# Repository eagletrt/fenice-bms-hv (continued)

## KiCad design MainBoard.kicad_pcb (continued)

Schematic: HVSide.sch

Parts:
C16, C23, C24, C26, C27, C40, C41, C44: 100nF; C_0603_1608Metric
C17: 1uF; C_0805_2012Metric
C42: 6.8uF; C_0805_2012Metric
C43: 10nF; C_0603_1608Metric
C45, C46: 10uF; C_0805_2012Metric
D4: LED_Small; LED_0603_1608Metric_Castellated
J4, J11: CONN_2X2; Molex_Micro-Fit_3.0_43045-0412_2x02_P3.00mm_Vertical
J17: HV; Molex_Mega-Fit_76829-0104_2x02_P5.70mm_Vertical
J18, J19: CONN_1X2; Molex_Micro-Fit_3.0_43650-0215_1x02_P3.00mm_Vertical
R10, R18, R26, R29, R57, R71: 100K; R_0603_1608Metric
R21, R59: 1K; R_0603_1608Metric
R24, R27: 10K; R_0603_1608Metric
R31, R32: 22; R_0603_1608Metric
R56, R64, R66: 10M; R_1206_3216Metric
R65, R67: 71K5; R_0603_1608Metric
R69: 2K; R_0603_1608Metric
R70: 680; R_0603_1608Metric
U7: ADCMP354; Analog_KS-4
U10: DCDC_ISO_5V_ISO; DC_DC_ISO_ROExxxx
U15: CD4082; TSSOP-14_4.4x5mm_P0.65mm
U16: ADCMP350; Analog_KS-4
U19, U26: TCMT1103; SOP-4_4.4x2.6mm_P1.27mm
U23: CD4072BPW; TSSOP-14_4.4x5mm_P0.65mm
U24: LTC6259; TSOT-23-8
U27: DCDC_ISO_5V; RFMM
U28: MIC5365-3.3YC5; SOT-353_SC-70-5
U29: Si8900; SOIC-16W_7.5x10.3mm_P1.27mm
U30: MAX14878AWA+; SOIC-8_7.5x5.85mm_P1.27mm

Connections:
+3V3: C16.1, C40.1, U29.10 (VDDB), U29.16 (VDDB), U30.3 (VDD1); also elsewhere on the board
+5V: C42.1, U27.1 (VIN+); also elsewhere on the board
+12V: C41.1, R24.1, R26.1, U15.4, U15.5, U15.14 (VCC), U23.14 (VDD); also elsewhere on the board
+BATT: J17.4, R64.2; also elsewhere on the board
+TS: J17.3, J18.1, J18.2, R56.1, R66.2; also elsewhere on the board
-BATT: C17.2, C23.2, C24.2, C26.2, C27.2, C44.2, C45.2, C46.2, J11.3, J17.1, R65.2, R67.2, U7.2 (GND), U10.3 (VOUT-), U16.2 (GND), U24.4, U26.3, U27.5 (VOUT-), U28.2 (GND), U29.8 (GNDA), U30.5 (GND2)
-TS: J17.2, J19.1, J19.2, R57.2
/AMS/ADC_RX: R32.1; also elsewhere on the board
/AMS/ADC_SIN: R29.1, R70.1; also elsewhere on the board
/AMS/ADC_TX: R31.1; also elsewhere on the board
/AMS/ISO_CAN_RX: U30.1 (RXD); also elsewhere on the board
/AMS/ISO_CAN_TX: U30.2 (TXD); also elsewhere on the board
/FB_AIR+: U23.3, U23.11; also elsewhere on the board
/FB_AIR-: U23.4, U23.10; also elsewhere on the board
/FB_TS_OVER_60V: R24.2, U15.2, U19.4, U23.5, U23.9; also elsewhere on the board
/HV/3V3ISO: C43.1, C46.1, R69.1, U28.5 (VOUT), U29.1 (VDDA)
/HV/5VISO: C26.1, C27.1, C44.1, C45.1, J11.4, R21.2, R71.2, U7.4 (VCC), U24.8, U27.7 (VOUT+), U28.1 (VIN), U30.8 (VCC2)
/HV/5V_FROM_CELL: C17.1, R59.1, U10.4 (VOUT+), U16.4 (VCC)
/HV/EXT_5V: J4.3, U10.2 (VIN+)
/HV/EXT_GND: J4.1, U10.1 (VIN-)
/HV/PRECHARGE_ON: U15.3; also elsewhere on the board
/HV/PRECHARGE_STATUS: R26.2, U15.1, U23.2, U23.12
/HV/PROMINENT+: J4.4, R59.2
/HV/PROMINENT-: J4.2, U16.3
/HV/PackV: R18.2, U24.1, U24.2
/HV/PackV_FT: C24.1, R18.1, U29.4 (AIN1)
/HV/TSV: R10.2, U24.6, U24.7
/HV/TSV_FT: C23.1, R10.1, U29.3 (AIN0)
/HV/TS_DIVIDER: R56.2, R57.1, U7.1 (VIN), U16.1 (VIN)
/HV/~RST~_8902: C43.2, R69.2, U26.4, U29.7 (~RST)
/IM: J11.1, U30.6 (CANL); also elsewhere on the board
/IP: J11.2, U30.7 (CANH); also elsewhere on the board
/LED_INDICATOR: U23.13; also elsewhere on the board
GND: C16.2, C40.2, C41.2, C42.2, R27.1, R29.2, U15.7 (VSS), U19.3, U23.7 (VSS), U26.2, U27.2 (VIN-), U29.9 (GNDB), U30.4 (GND1); also elsewhere on the board
unnamed: D4.1 (K), R27.2
unnamed: D4.2 (A), U23.1
unnamed: R21.1, U19.1
unnamed: R31.2, U29.13 (RX)
unnamed: R32.2, U29.12 (TX)
unnamed: R64.1, R65.1, U24.3
unnamed: R66.1, R67.1, U24.5
unnamed: R70.2, U26.1
unnamed: R71.1, U28.3 (EN)
unnamed: U7.3, U19.2

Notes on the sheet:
UART ISOLATED PACK VOLTAGE ADC
ISOLATED VOLTAGE SOURCES
"IN" connected to the NEGATIVE comparator input INTERNAL Vref=0.6V 1% High voltage (up to 22 V) tolerance on VIN
Prominent Indicator
HV ADC BUFFERS
PRECHARGE_STATUS = TS_exceed_60Vdc && PRECHARGE_ON
"IN" connected to thePOSITIVE comparator input INTERNAL Vref=0.6V 1% High voltage (up to 22 V) tolerance on VIN
IMD_TS-
IMD_TS+
EXT_POWER&PROMIMENT
CAN_ISO
PROMINENT INDICTOR

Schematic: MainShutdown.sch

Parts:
C32, C34, C35, C47: 100nF; C_0603_1608Metric
C33: 1uF; C_0805_2012Metric
D14: 12V; D_SOD-323
D15: D; SOD_323HE
J6, J10: CONN_2X2; Molex_Micro-Fit_3.0_43045-0412_2x02_P3.00mm_Vertical
K1: KT12-1A; KT_THT
K2: G6DN 12V; G6DN-1A_DC12
Q1: SSM3K361TU,LF; SOT-323_SC-70
Q2: TSM2312; TSOT-23
R9: 100K; R_0603_1608Metric
R54: 1M; R_0603_1608Metric
R55: 10K; pwr163
RN13: 100K; R_network_4x1_bourns_CAY16
U4: EL5421T; MSOP-10_3x3mm_P0.5mm
U13: TS3704IPT; TSSOP-14_4.4x5mm_P0.65mm
U14: CD4044; TSSOP-16_4.4x5mm_P0.65mm
U15: CD4082; TSSOP-14_4.4x5mm_P0.65mm

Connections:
+3V3: RN13.2 (R2.1), U13.4 (-); also elsewhere on the board
+12V: C32.1, C34.1, C35.1, C47.1, D15.1 (K), J6.1, J10.4, K2.2, R9.2, RN13.1 (R1.1), U4.3, U13.3 (V+), U14.5 (EN), U14.16 (Vdd), U15.14 (VCC); also elsewhere on the board
+BATT: K1.4; also elsewhere on the board
+TS: R55.2; also elsewhere on the board
/BMS_Fault: U13.7 (+); also elsewhere on the board
/BMS_LED: U4.9; also elsewhere on the board
/BSPD_SIG: U15.9; also elsewhere on the board
/FB_AIR+: J10.3; also elsewhere on the board
/FB_AIR-: J6.2; also elsewhere on the board
/FB_BMS: U13.1, U14.6; also elsewhere on the board
/FB_BMS_SD: U4.2, U15.12; also elsewhere on the board
/FB_IMD_SD: U4.4, U15.11; also elsewhere on the board
/FB_LACTH_BMS: U4.1, U4.10, U14.9; also elsewhere on the board
/FB_LACTH_IMD: U4.5, U4.6, U14.10; also elsewhere on the board
/FB_PC_END: Q1.1 (G), U13.13; also elsewhere on the board
/FB_SD_MINIRELAY: Q2.1 (G), U15.13; also elsewhere on the board
/FB_TS_ON: U13.14, U15.10; also elsewhere on the board
/FROM_SD: K2.3; also elsewhere on the board
/FROM_TSMS: J6.4, J10.1, K1.1, R54.2; also elsewhere on the board
/HV/PRECHARGE_ON: RN13.8 (R1.2), U13.2; also elsewhere on the board
/IMD_Fault: U14.12; also elsewhere on the board
/IMD_LED: U4.7; also elsewhere on the board
/NRST_SD: C33.1, R9.1, U14.7, U14.11; also elsewhere on the board
/PC_ENDED: U13.11 (+); also elsewhere on the board
/Shutdown/LAST_AIR: J10.2, Q1.3 (D)
/Shutdown/VREF_1.5V: RN13.6 (R3.2), RN13.7 (R2.2), U13.6 (-), U13.8 (-), U13.10 (-)
/Shutdown/dissipation: R55.3 (back)
/TO_TSMS: K2.4; also elsewhere on the board
/TS_ON: U13.9 (+); also elsewhere on the board
GND: C32.2, C33.2, C34.2, C35.2, C47.2, D14.2 (A), J6.3, K1.2, Q1.2 (S), Q2.2 (S), RN13.3 (R3.1), U4.8, U13.12 (V-), U14.8 (Vss), U15.7 (VSS); also elsewhere on the board
unnamed: D14.1 (K), R54.1, U13.5 (+)
unnamed: D15.2 (A), K2.1, Q2.3 (D)
unnamed: K1.3, R55.1

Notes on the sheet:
PWR163S-25-1002J
PRE-CHARGE CIRCUIT
TRACTIVE SYSTEM CONTROL
AIR CONTROL CIRCUIT
RESET BUTTON WITH PULLUP (100K) FOR AMS AND IMD FAULT WITH START DELAY OF 120ms (BECAUSE OF C=1uF AND VIH MIN OF 4044 is 8.4V AT VCC=12V)
LACTHING IC
SHUTDOWN STATUS
Vin=12V R=10K-->14.4mW Vref_1V5 R=100K-->0.06mW
AIR+
AIR-
Saves the fault status until reset from: BMS and IMD
TODO: no idea
TODO: still no idea probably for buffering before sending it out through the connector

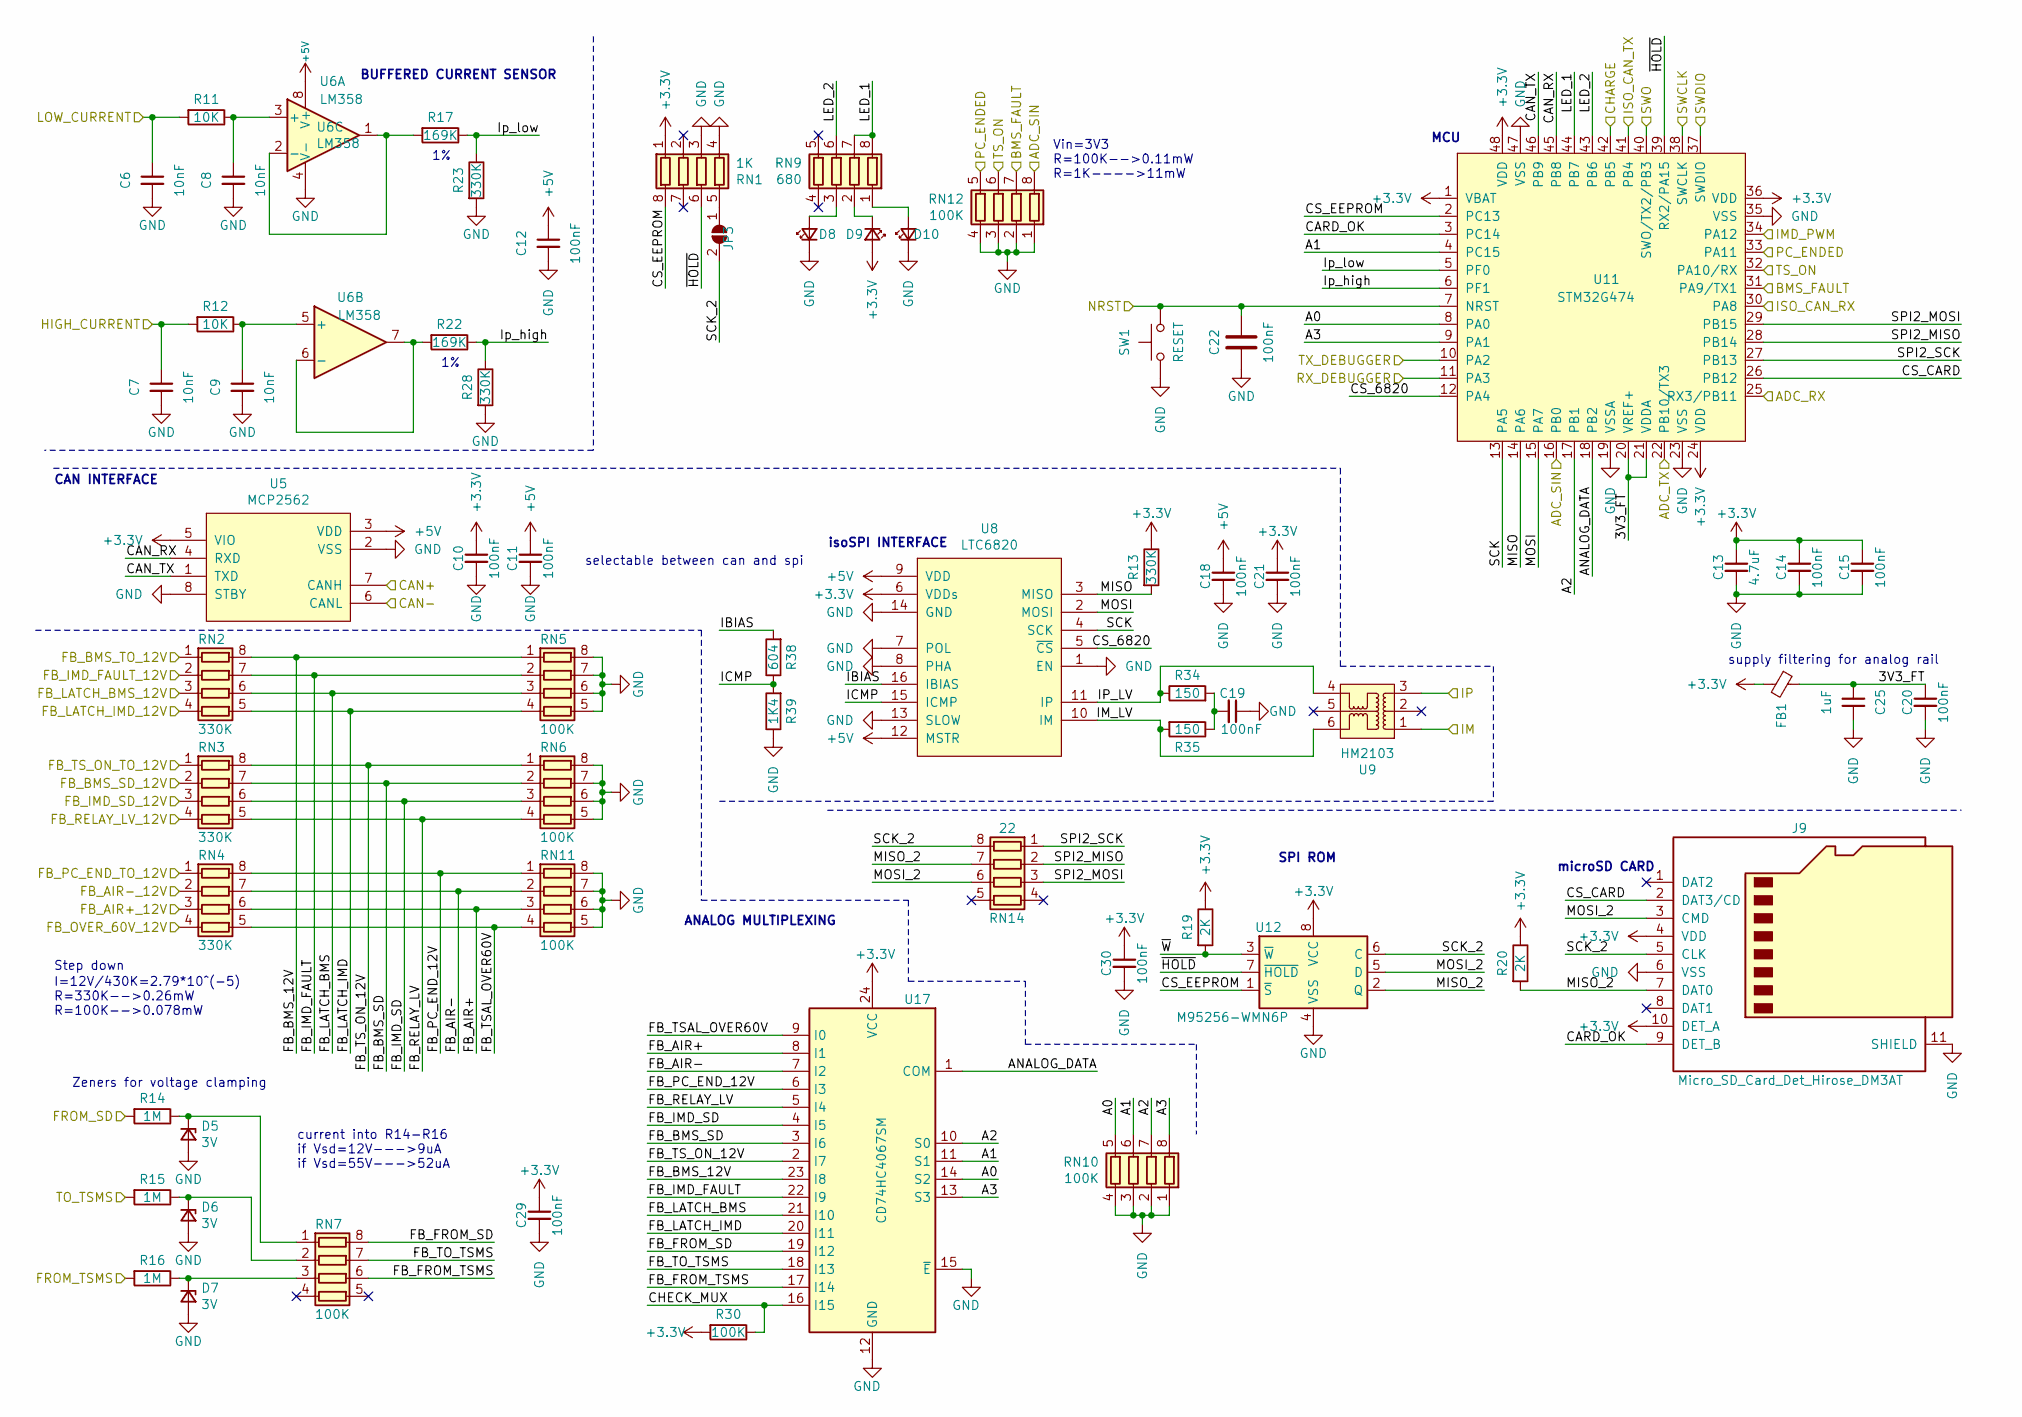
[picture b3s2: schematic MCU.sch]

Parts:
C6, C7, C8, C9: 10nF; C_0603_1608Metric
C10, C11, C12, C14, C15, C18, C19, C20, C21, C22, C29, C30: 100nF; C_0603_1608Metric
C13: 4.7uF; C_0805_2012Metric
C25: 1uF; C_0603_1608Metric
D5, D6, D7: 3V; D_SOD-323
D8: LED_Small; LED_REVERSE_MOUNT_cilindrical
D9, D10: LED_Small; LED_0603_1608Metric_Castellated
FB1: FerriteBead_Small; L_0603_1608Metric_Pad1.05x0.95mm_HandSolder
J9: Micro_SD_Card_Det_Hirose_DM3AT; MicroSD_Hirose_DM3AT-SF-PEJM5
JP3: SolderJumper_2_Open; Jumper_SMD_0603
R11, R12: 10K; R_0603_1608Metric
R13, R23, R28: 330K; R_0603_1608Metric
R14, R15, R16: 1M; R_0603_1608Metric
R17, R22: 169K; R_0603_1608Metric
R19, R20: 2K; R_0603_1608Metric
R30: 100K; R_0603_1608Metric
R34, R35: 150; R_0603_1608Metric
R38: 604; R_0603_1608Metric
R39: 1K4; R_0603_1608Metric
RN1: 1K; R_network_4x1_bourns_CAY16
RN2, RN3, RN4: 330K; R_network_4x1_bourns_CAY16
RN5, RN6, RN7, RN10, RN11, RN12: 100K; R_network_4x1_bourns_CAY16
RN9: 680; R_network_4x1_bourns_CAY16
RN14: 22; R_network_4x1_bourns_CAY16
SW1: RESET; Button_SMD_6x3.5x4.3mm
U5: MCP2562; SOIC-8_3.9x4.9mm_P1.27mm
U6: LM358; TSOT-23-8
U8: LTC6820; MSOP-16
U9: HM2103
U11: STM32G474; LQFP-48_7x7mm_P0.5mm
U12: M95256-WMN6P; TSSOP-8_4.4x3mm_P0.65mm
U17: CD74HC4067SM; TSSOP-24_4.4x7.8mm_P0.65mm

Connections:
+3V3: C10.1, C13.1, C14.1, C15.1, C21.1, C29.1, C30.1, D9.2 (A), FB1.2, J9.4 (VDD), J9.10 (DET_A), R13.1, R19.1, R20.1, R30.2, RN1.1 (R1.1), U5.5 (VIO), U8.6 (VDDs), U11.1 (VBAT), U11.24 (VDD), U11.36 (VDD), U11.48 (VDD), U12.8 (VCC), U17.24 (VCC); also elsewhere on the board
+5V: C11.1, C12.1, C18.1, U5.3 (VDD), U6.8 (V+), U8.9 (VDD), U8.12 (MSTR); also elsewhere on the board
/AMS/3V3_FT: C20.1, C25.2, FB1.1, U11.20 (VREF+), U11.21 (VDDA)
/AMS/A0: RN10.5 (R4.2), U11.8 (PA0), U17.14 (S2)
/AMS/A1: RN10.6 (R3.2), U11.4 (PC15), U17.11 (S1)
/AMS/A2: RN10.7 (R2.2), U11.17 (PB1), U17.10 (S0)
/AMS/A3: RN10.8 (R1.2), U11.9 (PA1), U17.13 (S3)
/AMS/ADC_RX: U11.25 (RX3/PB11); also elsewhere on the board
/AMS/ADC_SIN: RN12.8 (R1.2), U11.16 (PB0); also elsewhere on the board
/AMS/ADC_TX: U11.22 (PB10/TX3); also elsewhere on the board
/AMS/ANALOG_DATA: U11.18 (PB2), U17.1 (COM)
/AMS/CAN_RX: U5.4 (RXD), U11.45 (PB8)
/AMS/CAN_TX: U5.1 (TXD), U11.46 (PB9)
/AMS/CARD_OK: J9.9 (DET_B), U11.3 (PC14)
/AMS/CHECK_MUX: R30.1, U17.16 (I15)
/AMS/CS_6820: U8.5 (~CS), U11.12 (PA4)
/AMS/CS_CARD: J9.2 (DAT3/CD), U11.26 (PB12)
/AMS/CS_EEPROM: RN1.8 (R1.2), U11.2 (PC13), U12.1 (~S)
/AMS/FB_AIR+: RN4.6 (R3.2), RN11.3 (R3.1), U17.8 (I1)
/AMS/FB_AIR-: RN4.7 (R2.2), RN11.2 (R2.1), U17.7 (I2)
/AMS/FB_BMS_12V: RN2.8 (R1.2), RN5.1 (R1.1), U17.23 (I8)
/AMS/FB_BMS_SD: RN3.7 (R2.2), RN6.2 (R2.1), U17.3 (I6)
/AMS/FB_FROM_SD: RN7.8 (R1.2), U17.19 (I12)
/AMS/FB_FROM_TSMS: RN7.6 (R3.2), U17.17 (I14)
/AMS/FB_IMD_FAULT: RN2.7 (R2.2), RN5.2 (R2.1), U17.22 (I9)
/AMS/FB_IMD_SD: RN3.6 (R3.2), RN6.3 (R3.1), U17.4 (I5)
/AMS/FB_LATCH_BMS: RN2.6 (R3.2), RN5.3 (R3.1), U17.21 (I10)
/AMS/FB_LATCH_IMD: RN2.5 (R4.2), RN5.4 (R4.1), U17.20 (I11)
/AMS/FB_PC_END_12V: RN4.8 (R1.2), RN11.1 (R1.1), U17.6 (I3)
/AMS/FB_RELAY_LV: RN3.5 (R4.2), RN6.4 (R4.1), U17.5 (I4)
/AMS/FB_TO_TSMS: RN7.7 (R2.2), U17.18 (I13)
/AMS/FB_TSAL_OVER60V: RN4.5 (R4.2), RN11.4 (R4.1), U17.9 (I0)
/AMS/FB_TS_ON_12V: RN3.8 (R1.2), RN6.1 (R1.1), U17.2 (I7)
/AMS/IBIAS: R38.2, U8.16 (IBIAS)
/AMS/ICMP: R38.1, R39.2, U8.15 (ICMP)
/AMS/IM_LV: R35.2, U8.10 (IM), U9.6
/AMS/IP_LV: R34.1, U8.11 (IP), U9.4
/AMS/ISO_CAN_RX: U11.30 (PA8); also elsewhere on the board
/AMS/ISO_CAN_TX: U11.41 (PB4); also elsewhere on the board
/AMS/Ip_high: R22.1, R28.1, U11.6 (PF1)
/AMS/Ip_low: R17.1, R23.1, U11.5 (PF0)
/AMS/LED_1: RN9.7 (R2.2), RN9.8 (R1.2), U11.44 (PB7)
/AMS/LED_2: RN9.6 (R3.2), U11.43 (PB6)
/AMS/MISO: R13.2, U8.3 (MISO), U11.14 (PA6)
/AMS/MISO_2: J9.7 (DAT0), R20.2, RN14.7 (R2.2), U12.2 (Q)
/AMS/MOSI: U8.2 (MOSI), U11.15 (PA7)
/AMS/MOSI_2: J9.3 (CMD), RN14.6 (R3.2), U12.5 (D)
/AMS/SCK: U8.4 (SCK), U11.13 (PA5)
/AMS/SCK_2: J9.5 (CLK), JP3.2 (B), RN14.8 (R1.2), U12.6 (C)
/AMS/SPI2_MISO: RN14.2 (R2.1), U11.28 (PB14)
/AMS/SPI2_MOSI: RN14.3 (R3.1), U11.29 (PB15)
/AMS/SPI2_SCK: RN14.1 (R1.1), U11.27 (PB13)
/AMS/~HOLD~: RN1.6 (R3.2), U11.39 (RX2/PA15), U12.7 (~HOLD)
/AMS/~W~: R19.2, U12.3 (~W)
/BMS_Fault: RN12.7 (R2.2), U11.31 (PA9/TX1); also elsewhere on the board
/CAN+: U5.7 (CANH); also elsewhere on the board
/CAN-: U5.6 (CANL); also elsewhere on the board
/CHARGE: U11.42 (PB5); also elsewhere on the board
/FB_AIR+: RN4.3 (R3.1); also elsewhere on the board
/FB_AIR-: RN4.2 (R2.1); also elsewhere on the board
/FB_BMS: RN2.1 (R1.1); also elsewhere on the board
/FB_BMS_SD: RN3.2 (R2.1); also elsewhere on the board
/FB_IMD_SD: RN3.3 (R3.1); also elsewhere on the board
/FB_LACTH_BMS: RN2.3 (R3.1); also elsewhere on the board
/FB_LACTH_IMD: RN2.4 (R4.1); also elsewhere on the board
/FB_PC_END: RN4.1 (R1.1); also elsewhere on the board
/FB_SD_MINIRELAY: RN3.4 (R4.1); also elsewhere on the board
/FB_TS_ON: RN3.1 (R1.1); also elsewhere on the board
/FB_TS_OVER_60V: RN4.4 (R4.1); also elsewhere on the board
/FROM_SD: R14.2; also elsewhere on the board
/FROM_TSMS: R16.2; also elsewhere on the board
/HIGH_CURRENT: C7.1, R12.2; also elsewhere on the board
/IM: U9.1; also elsewhere on the board
/IMD: U11.34 (PA12); also elsewhere on the board
/IMD_Fault: RN2.2 (R2.1); also elsewhere on the board
/IP: U9.3; also elsewhere on the board
/LOW_CURRENT: C6.1, R11.2; also elsewhere on the board
/NRST_MCU: C22.1, SW1.1, U11.7 (NRST); also elsewhere on the board
/PC_ENDED: RN12.5 (R4.2), U11.33 (PA11); also elsewhere on the board
/RX_MCU: U11.11 (PA3); also elsewhere on the board
/SWCLK_MCU: U11.38 (SWCLK); also elsewhere on the board
/SWDIO_MCU: U11.37 (SWDIO); also elsewhere on the board
/SWO_MCU: U11.40 (SWO/TX2/PB3); also elsewhere on the board
/TO_TSMS: R15.2; also elsewhere on the board
/TS_ON: RN12.6 (R3.2), U11.32 (PA10/RX); also elsewhere on the board
/TX_MCU: U11.10 (PA2); also elsewhere on the board
GND: C6.2, C7.2, C8.2, C9.2, C10.2, C11.2, C12.2, C13.2, C14.2, C15.2, C18.2, C19.1, C20.2, C21.2, C22.2, C25.1, C29.2, C30.2, D5.2 (A), D6.2 (A), D7.2 (A), D8.1 (K), D10.1 (K), J9.6 (VSS), J9.11 (SHIELD), R23.2, R28.2, R39.1, RN1.3 (R3.1), RN1.4 (R4.1), RN5.5 (R4.2), RN5.6 (R3.2), RN5.7 (R2.2), RN5.8 (R1.2), RN6.5 (R4.2), RN6.6 (R3.2), RN6.7 (R2.2), RN6.8 (R1.2), RN10.1 (R1.1), RN10.2 (R2.1), RN10.3 (R3.1), RN10.4 (R4.1), RN11.5 (R4.2), RN11.6 (R3.2), RN11.7 (R2.2), RN11.8 (R1.2), RN12.1 (R1.1), RN12.2 (R2.1), RN12.3 (R3.1), RN12.4 (R4.1), SW1.2, U5.2 (VSS), U5.8 (STBY), U6.4 (V-), U8.1 (EN), U8.7 (POL), U8.8 (PHA), U8.13 (SLOW), U8.14 (GND), U11.19 (VSSA), U11.23 (VSS), U11.35 (VSS), U11.47 (VSS), U12.4 (VSS), U17.12 (GND), U17.15 (~E); also elsewhere on the board
unnamed: C8.1, R11.1, U6.3 (+)
unnamed: C9.1, R12.1, U6.5 (+)
unnamed: C19.2, R34.2, R35.1
unnamed: D5.1 (K), R14.1, RN7.1 (R1.1)
unnamed: D6.1 (K), R15.1, RN7.2 (R2.1)
unnamed: D7.1 (K), R16.1, RN7.3 (R3.1)
unnamed: D8.2 (A), RN9.3 (R3.1)
unnamed: D9.1 (K), RN9.2 (R2.1)
unnamed: D10.2 (A), RN9.1 (R1.1)
unnamed: JP3.1 (A), RN1.5 (R4.2)
unnamed: R17.2, U6.1, U6.2 (-)
unnamed: R22.2, U6.6 (-), U6.7

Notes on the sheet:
isoSPI INTERFACE
CAN INTERFACE
BUFFERED CURRENT SENSOR
microSD CARD
current into R14-R16 if Vsd=12V--->9uA if Vsd=55V--->52uA
I=12V/430K=2.79*10^(-5) R=330K-->0.26mW R=100K-->0.078mW
Vin=3V3 R=100K-->0.11mW R=1K---->11mW
ANALOG MULTIPLEXING
Step down
Zeners for voltage clamping
MCU
supply filtering for analog rail
SPI ROM
selectable between can and spi

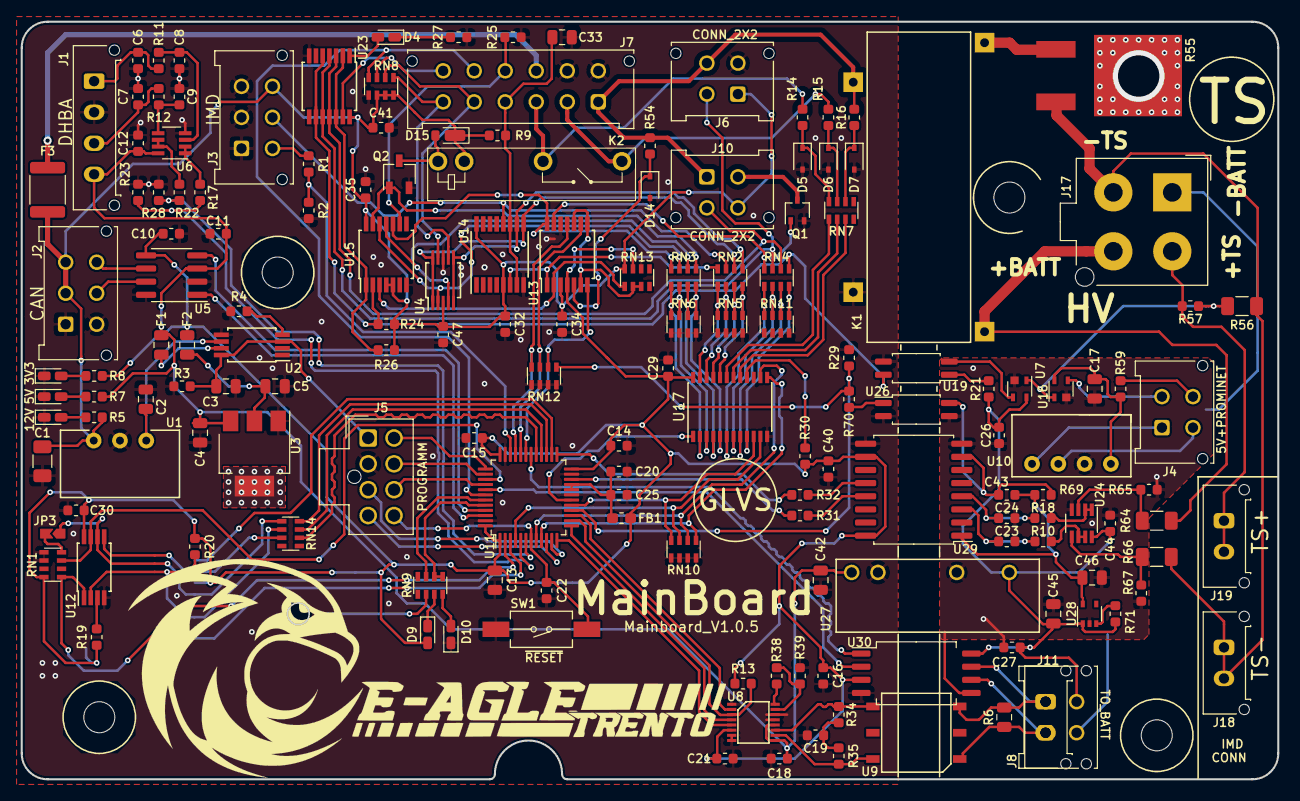
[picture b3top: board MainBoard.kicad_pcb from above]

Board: 2 copper layers, 121.5 x 73.2 mm, 168 parts (1 on the bottom side), 149 nets.

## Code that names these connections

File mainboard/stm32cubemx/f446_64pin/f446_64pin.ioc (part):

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Mcu.Name=STM32F446R(C-E)Tx
Mcu.Package=LQFP64
Mcu.UserName=STM32F446RETx
PA0-WKUP.GPIOParameters=GPIO_Label
PA0-WKUP.GPIO_Label=FB_RELAY_LV
PA0-WKUP.Signal=ADCx_IN0
PA1.GPIOParameters=GPIO_Label
PA1.GPIO_Label=FB_FROM_TSMS
PA1.Signal=ADCx_IN1
PA10.GPIOParameters=GPIO_Label
PA10.GPIO_Label=RX_SWD
PA10.Mode=Asynchronous
PA10.Signal=USART1_RX
PA11.GPIOParameters=GPIO_Label
PA11.GPIO_Label=CAN_RX
PA11.Mode=CAN_Activate
PA11.Signal=CAN1_RX
PA12.GPIOParameters=GPIO_Label
PA12.GPIO_Label=CAN_TX
PA12.Mode=CAN_Activate
PA12.Signal=CAN1_TX
PA13.Mode=Serial_Wire
PA13.Signal=SYS_JTMS-SWDIO
PA14.Mode=Serial_Wire
PA14.Signal=SYS_JTCK-SWCLK
PA2.GPIOParameters=GPIO_Label
PA2.GPIO_Label=FB_IMD_FAULT
PA2.Signal=ADCx_IN2
PA3.Signal=ADCx_IN3
PA4.GPIOParameters=GPIO_Label
PA4.GPIO_Label=MUX_INPUT
PA4.Signal=ADCx_IN4
PA5.Mode=Full_Duplex_Master
PA5.Signal=SPI1_SCK
PA6.Mode=Full_Duplex_Master
PA6.Signal=SPI1_MISO
PA7.Mode=Full_Duplex_Master
PA7.Signal=SPI1_MOSI
PA9.GPIOParameters=GPIO_Label
PA9.GPIO_Label=TX_SWD
PA9.Mode=Asynchronous
PA9.Signal=USART1_TX
PB13.Mode=Full_Duplex_Master
PB13.Signal=SPI2_SCK
PB14.Mode=Full_Duplex_Master
PB14.Signal=SPI2_MISO
PB15.Mode=Full_Duplex_Master
PB15.Signal=SPI2_MOSI
PB2.GPIOParameters=GPIO_Label
PB2.GPIO_Label=IMD_PWM
PB2.Signal=S_TIM2_CH4
PB3.Signal=SYS_JTDO-SWO
PB5.GPIOParameters=GPIO_Label
PB5.GPIO_Label=CAN_CELL_RX
PB5.Mode=CAN_Activate
PB5.Signal=CAN2_RX
PB6.GPIOParameters=GPIO_Label
PB6.GPIO_Label=CAN_CELL_TX
PB6.Mode=CAN_Activate
PB6.Signal=CAN2_TX
PB8.GPIOParameters=GPIO_Label
PB8.GPIO_Label=LED2
PB8.Signal=S_TIM4_CH3
PB9.GPIOParameters=GPIO_Label
PB9.GPIO_Label=LED1
PB9.Signal=S_TIM4_CH4
PC1.GPIOParameters=GPIO_Label
PC1.GPIO_Label=CHARGE
PC1.Signal=ADCx_IN11
PC10.GPIOParameters=GPIO_Label
PC10.GPIO_Label=BMS_FAULT
PC10.Signal=GPIO_Output
PC11.GPIOParameters=GPIO_Label
PC11.GPIO_Label=TS_ON
PC11.Signal=GPIO_Output
PC12.GPIOParameters=GPIO_Label
PC12.GPIO_Label=AIRP_OFF
PC12.Signal=GPIO_Output
PC2.GPIOParameters=GPIO_Label
PC2.GPIO_Label=IP_LOW
PC2.Signal=ADCx_IN12
PC3.GPIOParameters=GPIO_Label
PC3.GPIO_Label=IP_HIGH
PC3.Signal=ADCx_IN13
PC4.GPIOParameters=GPIO_Label
PC4.GPIO_Label=CS_ADC
PC4.Signal=GPIO_Output
PC6.GPIOParameters=GPIO_Label
PC6.GPIO_Label=CS_EEPROM
PC6.Signal=GPIO_Output
PC7.GPIOParameters=GPIO_Label
PC7.GPIO_Label=HOLD
PC7.Signal=GPIO_Output
PC8.GPIOParameters=GPIO_Label
PC8.GPIO_Label=CS_CARD
PC8.Signal=GPIO_Output
PC9.GPIOParameters=GPIO_Label
PC9.GPIO_Label=CARD_OK
PC9.Signal=GPIO_Input
PD2.GPIOParameters=PinState,GPIO_Label
PD2.GPIO_Label=AIRN_OFF
PD2.PinState=GPIO_PIN_SET
PD2.Signal=GPIO_Output
PH0-OSC_IN.Mode=HSE-External-Oscillator
PH0-OSC_IN.Signal=RCC_OSC_IN
PH1-OSC_OUT.Mode=HSE-External-Oscillator
PH1-OSC_OUT.Signal=RCC_OSC_OUT
RCC.HSE_VALUE=26000000
RCC.SYSCLKFreq_VALUE=16000000
board=custom

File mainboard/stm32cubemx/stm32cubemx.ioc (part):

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PA6.Mode=Full_Duplex_Master
Mcu.UserName=STM32G474RETx
PB10.Mode=Asynchronous
PA14.GPIO_Label=SWCLK
PA11.Mode=FDCAN_Activate
PG10-NRST.GPIO_Label=NRST
PC5.Mode=Asynchronous
PB11.Signal=USART3_RX
PB13.Signal=SPI2_SCK
PB15.Signal=SPI2_MOSI
PA12.Signal=FDCAN1_TX
PB6.Signal=FDCAN2_TX
PB6.Mode=FDCAN_Activate
PB8-BOOT0.GPIOParameters=GPIO_Label
RCC.HSE_VALUE=8000000
PB3.Mode=Trace_Asynchronous_SW
PB2.Signal=ADC2_IN12
PB12.GPIO_Label=CS_CARD
PA14.Mode=Trace_Asynchronous_SW
PB14.Mode=Full_Duplex_Master
PB5.Mode=FDCAN_Activate
PB3.GPIOParameters=GPIO_Label
PA13.GPIOParameters=GPIO_Label
Mcu.Package=LQFP64
PA6.Signal=SPI1_MISO
PB8-BOOT0.GPIO_Label=BOOT0
PC5.Signal=USART1_RX
PB13.Mode=Full_Duplex_Master
PF1-OSC_OUT.Mode=HSE-External-Oscillator
PF1-OSC_OUT.Signal=RCC_OSC_OUT
PC4.Mode=Asynchronous
PA5.Mode=Full_Duplex_Master
PB3.GPIO_Label=SWO
PA7.Mode=Full_Duplex_Master
PC4.Signal=USART1_TX
PA13.Signal=SYS_JTMS-SWDIO
PB11.Mode=Asynchronous
PG10-NRST.Signal=GPIO_Input
PF0-OSC_IN.Mode=HSE-External-Oscillator
PB10.Signal=USART3_TX
PB14.Signal=SPI2_MISO
PA5.Signal=SPI1_SCK
PB8-BOOT0.Signal=GPIO_Input
board=custom
PB15.Mode=Full_Duplex_Master
PA13.Mode=Trace_Asynchronous_SW
Mcu.Name=STM32G474R(B-C-E)Tx
PA13.GPIO_Label=SWDIO
PB3.Signal=SYS_JTDO-SWO
RCC.SYSCLKFreq_VALUE=16000000
PB5.Signal=FDCAN2_RX
PA12.Mode=FDCAN_Activate
PA14.GPIOParameters=GPIO_Label
PB2.Mode=IN12-Single-Ended
PA11.Signal=FDCAN1_RX
PA14.Signal=SYS_JTCK-SWCLK
PG10-NRST.GPIOParameters=GPIO_Label
PF0-OSC_IN.Signal=RCC_OSC_IN
PB12.GPIOParameters=GPIO_Label
PB12.Signal=GPIO_Output
PA7.Signal=SPI1_MOSI

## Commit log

2020-10-15 First commit, git setup for kicad
2020-10-15 Converted to git, corrected a whole ton of rando symbols origins
2020-10-16 added a lot of annotations and readability in the schematic, not complete
2020-10-19 Logo wasn't virtual, new netlist
2020-11-11 Updated the project to updates in the kicad libraries
2020-11-11 updated to new components as per v1.0.5
2020-11-11 Updated all to the last new v1.0.5 as printed by taba
2020-12-01 Board as soldered
2020-12-03 first commit on new master
2020-12-03 first commit on hardware master
2020-12-03 added documentation/specification folder
2020-12-03 added dcoumentation and first refs submodules
2020-12-04 Moved mainboard stuff to its own folder
2020-12-04 moved mainboard/datasheet files to docs/, mainboard/docs does not contain datasheets now
2020-12-04 Updated readme in regards to datasheets folder
2020-12-04 Updated the readmes for the new repo structure
2020-12-05 updated tagging definition in README
2020-12-09 Added datasheet for STM32G4
2020-12-09 Corrected BOOT0
2020-12-10 Added jumper for BOOT0 to 3V3
2020-12-10 Added vias due to last boot0 modification
2020-12-10 Added 64pin mcu and moved isocanspi to HV sheet
2020-12-23 added the stm32 configuration, neaten schematic
2021-03-03 docs
2021-03-06 gitignore gitattributes added
2021-03-06 cellboard initial commit
2021-03-06 excluding whole board step file
2021-03-06 general changes and comments, still WIP
2021-03-06 ddding atasheet
2021-03-06 adding output directory, ignore for librecad tempfiles
2021-03-06 repaired tree format
2021-03-06 removed rescue references and rescue library
2021-03-06 rewrited README
2021-03-06 added version number, as printed
2021-03-07 64pin, testpoints, commenting, general refactoring
2021-03-11 renamed shutdown nets
2021-03-11 added image of shutdown path
2021-03-12 adding shutdown image
2021-03-12 adding testpoints
2021-03-12 minor changes
2021-03-12 changed Q2
2021-03-13 redone the air connections for clarity
2021-03-15 Redone the CD4072, it can't light a LED as per datasheet
2021-03-16 Initial database refactor
2021-03-16 error: fix very bad bugs
2021-03-16 pack: refactor voltage management
2021-03-16 docs: move comments around
2021-03-27 added precharge rele suppression diode
2021-03-27 commented AIR suppression
2021-03-28 modifieed comment
2021-03-29 docs: add build action
2021-04-21 updated libraries
2021-04-21 libraries requirements
2021-04-21 new standard connector
2021-04-23 Initial docs commit
2021-04-23 Deploying to docs from @ eagletrt/fenice-bms-hv@f15c2d177b0f3eff08955f7d56c120cb51bc8789 🚀
2021-04-25 added datasheets
2021-04-25 Add initial can management functions
2021-04-25 can: further expand can management
2021-04-25 Fix flatbuffers skeleton
2021-04-25 can: make everything work
2021-04-25 Update stmignore
2021-04-25 can: update cicd
2021-04-25 can: check instance inside interrupt
2021-04-25 can: move away from flatcc
2021-04-25 can: glue can to fsm
2021-04-25 can: fix decoding
2021-04-25 core: fix stmignore
2021-04-25 Deploying to docs from @ eagletrt/fenice-bms-hv@f7e9449503bc6f6a9dd0a0a152e2d099d53870ab 🚀
2021-04-25 Fix cli
2021-04-25 Deploying to docs from @ eagletrt/fenice-bms-hv@abc1b564eae1086dee7a8c7e1c1e08ef7d595bab 🚀
2021-04-25 cli: add dmesg debug feature
2021-04-25 Deploying to docs from @ eagletrt/fenice-bms-hv@9dfdafd8e50eecb9f3f69136ea0da5603597b570 🚀
2021-04-25 cli: general improvements
2021-04-25 Deploying to docs from @ eagletrt/fenice-bms-hv@f39d989bc96c7e96bc4a62d03f07589fd4fd9360 🚀
2021-05-06 Deploying to docs from @ eagletrt/fenice-bms-hv@00b6a3b2e6b2b1175d1124f767c5eae5f0f41875 🚀
2021-05-08 Deploying to docs from @ eagletrt/fenice-bms-hv@52499e30792cf478ac83ca9a8d31154b15923561 🚀
2021-05-08 Deploying to docs from @ eagletrt/fenice-bms-hv@8736ec241bd6fce57326ebd52ef403e15f4c659e 🚀
2021-05-09 Deploying to docs from @ eagletrt/fenice-bms-hv@88b6e2129cb3ae3ff915d475dbb9e5c8462e8f7f 🚀
2021-05-11 Deploying to docs from @ eagletrt/fenice-bms-hv@183dc2a54fd169e48f1a77dfed97a7b075d3e3ae 🚀
2021-05-12 Deploying to docs from @ eagletrt/fenice-bms-hv@e161e0d1ce229ac121417d6a929da7ef41244b29 🚀
2021-05-12 Deploying to docs from @ eagletrt/fenice-bms-hv@cff11fd7197ebad03b9ef91b5f5954999a711d5a 🚀
2021-05-12 Deploying to docs from @ eagletrt/fenice-bms-hv@137b0da16d5c895be2e0bf27079a77fb355822e3 🚀
2021-05-15 Deploying to docs from @ eagletrt/fenice-bms-hv@c7a369ccb4c38320be12d18942a38e54dc5396f9 🚀
2021-05-15 Deploying to docs from @ eagletrt/fenice-bms-hv@657732bc8d34db2a6c97fc87474325852d8eaf75 🚀
2021-05-15 Deploying to docs from @ eagletrt/fenice-bms-hv@ebb8ef127e51a5344346e598767b01d17adf0b31 🚀
2021-05-15 Deploying to docs from @ eagletrt/fenice-bms-hv@01bf477fcd5b6edfb6efc3ab0855644fc72c3760 🚀
2021-05-17 eeprom: add m95256
2021-05-17 Deploying to docs from @ eagletrt/fenice-bms-hv@e0af827685fd9762fc97e10b54367a276a916ba8 🚀
2021-05-17 eeprom: make it work
2021-05-17 Deploying to docs from @ eagletrt/fenice-bms-hv@e21ec54e8905bfca71d71890ba68db80da8f1e2b 🚀
2021-05-17 eeprom: move library to micro-libs
2021-05-17 Deploying to docs from @ eagletrt/fenice-bms-hv@52ea5b5ec9c57b06c368af47f887d65525de9c44 🚀
2021-05-28 Deploying to docs from @ eagletrt/fenice-bms-hv@c2270ba8371468e11b6ad22cd108d46041fe75e2 🚀
2021-05-29 eeprom: add config interface
2021-05-29 Deploying to docs from @ eagletrt/fenice-bms-hv@031bcbc19475deebcecdc69f92938db44b0aa4c9 🚀
2021-05-29 Deploying to docs from @ eagletrt/fenice-bms-hv@8b8d82278898c2ea52113e52bbe60b0001a9d375 🚀
2021-05-29 Deploying to docs from @ eagletrt/fenice-bms-hv@c408424412fe9eed25628619d5ceba217959cd1e 🚀
2021-05-30 Deploying to docs from @ eagletrt/fenice-bms-hv@785e2cc73ef59925169aaf4c6981360f22952385 🚀
2021-05-30 Deploying to docs from @ eagletrt/fenice-bms-hv@51786e05c05c0577b8a86e23cb7494acad133186 🚀
2021-05-30 Deploying to docs from @ eagletrt/fenice-bms-hv@4699930bd73e540c298527a0fd0fd576cfb3a7ac 🚀
2021-05-30 Deploying to docs from @ eagletrt/fenice-bms-hv@32d866aaede4b9a0f7d8d4a324fb6f7e316edee0 🚀
2021-06-11 Deploying to docs from @ eagletrt/fenice-bms-hv@2c03c48ae00988e968572ee58b3281b31db77067 🚀
2021-06-11 Deploying to docs from @ eagletrt/fenice-bms-hv@83e6063c72277a3028124e47e36732545637bb3b 🚀
2021-06-12 Deploying to docs from @ eagletrt/fenice-bms-hv@74c5e2e554ca0e7c8ce8166f95fee1b0d5ab3023 🚀
2021-06-12 Deploying to docs from @ eagletrt/fenice-bms-hv@f5f30973c6d090eb9770cf9a1870b3256df7756b 🚀
2021-06-12 Deploying to docs from @ eagletrt/fenice-bms-hv@3019bd4deb92247b86970d4146653a4793b2227f 🚀
2021-06-22 v1.1 as printed
2021-06-22 v2.1.2.5 as printed
    Commit on behalf of fran-retfie.
2021-06-22 modified version number
2021-06-28 changed footprint mcp1811
2021-06-28 Deploying to docs from @ eagletrt/fenice-bms-hv@8cdb73dbe13b5a9561da8585393a9c013eb1cbf3 🚀
2021-06-29 moved labels R5 C23
2021-07-28 Renamed handcart detection
2021-07-28 Deploying to docs from @ eagletrt/fenice-bms-hv@ea548f7b5dbf336ee0160c7f1f08a8a7fcff53dd 🚀
2021-09-13 Deploying to docs from @ eagletrt/fenice-bms-hv@d22d023334bb8cebe8f3e0cb4a92ba4e9ed7ce5f 🚀
2021-09-13 Deploying to docs from @ eagletrt/fenice-bms-hv@bea5481e6053cdedec70c48cd4da896c3b389872 🚀
2021-09-25 Deploying to docs from @ eagletrt/fenice-bms-hv@0509a0651be2edcbd3b963c28a7c65b585f54e12 🚀
2021-09-25 Deploying to docs from @ eagletrt/fenice-bms-hv@85ac93ac990b8b69bb4d234bdf7b06ca2fd542a3 🚀
2021-09-25 Deploying to docs from @ eagletrt/fenice-bms-hv@c3bf94e4bee88b9d2adde58154afaf597ea30506 🚀
2021-09-25 Deploying to docs from @ eagletrt/fenice-bms-hv@0f734274a400e548147808172a40a99a75c2880b 🚀
2021-10-03 docs: initial commit
2021-10-05 Deploying to docs from @ eagletrt/fenice-bms-hv@9db7226c6969de0e2cfb7104837c2a456b438a8c 🚀
2021-10-08 docs: update
2021-10-09 Deploying to docs from @ eagletrt/fenice-bms-hv@46a842aec80b103ec978d819e7da9a9bc5fa1402 🚀
2021-10-09 Deploying to docs from @ eagletrt/fenice-bms-hv@65c768afbe307878bcdaeb06dc06b6e4f751a90d 🚀
2021-10-11 docs: fix image link
2021-10-11 Deploying to docs from @ eagletrt/fenice-bms-hv@936b902ab36bb40a05d4fb916562338e71587619 🚀
2021-10-11 Deploying to docs from @ eagletrt/fenice-bms-hv@45a431e30ef8e717b608be1e878342da3c058fb1 🚀
2021-10-14 Deploying to docs from @ eagletrt/fenice-bms-hv@405232bf643ab8659186d9e3a7ce1d810f7b4297 🚀
2021-10-15 Deploying to docs from @ eagletrt/fenice-bms-hv@6c22d67ccaf41dcd9fa322646f822d2ce2f36021 🚀
2021-10-16 Correction almost finished, Started layouting
2021-10-23 Deploying to docs from @ eagletrt/fenice-bms-hv@a29371e3a65518984a753c290784bbb40cfdd7e6 🚀
2021-10-26 Deploying to docs from @ eagletrt/fenice-bms-hv@f9798bfd721d659fe74386bdab05acac1832acfb 🚀
2021-10-26 Deploying to docs from @ eagletrt/fenice-bms-hv@683eace7c3e81a6db53b4ef1c6cfb927de5b1cef 🚀
2021-10-26 Deploying to docs from @ eagletrt/fenice-bms-hv@3a82b036ee2384a92b3a59c2fa18593488ccc603 🚀
